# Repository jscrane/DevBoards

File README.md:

View this project on [CADLAB.io](https://cadlab.io/project/23203). 

# DevBoards
Development and breakout boards for use in Arduino projects, with Gerbers.

## t84opti
An ATtiny84 development board with FTDI interface. Works very well
with [Optiboot](https://github.com/Optiboot/optiboot),
in particular with the [ATTinyCore](https://github.com/SpenceKonde/ATTinyCore). (Top, in picture.)

## t85opti
Same as t84opti, except with ATtiny85, and no LED_BUILTIN. (Bottom, in picture.)

## nrf24l01
A breadboard adapter for the
[nrf24l01](https://howtomechatronics.com/tutorials/arduino/arduino-wireless-communication-nrf24l01-tutorial/)
short-range wireless module. (Right, in picture.)

## ncp1402
A breadboard adapter for the [ncp1402](https://www.onsemi.com/pub/Collateral/NCP1402-D.PDF)
step-up switching regulator ("boost converter"). (Left, in picture.) <i>Warning: SMD soldering required!</i>

## nrf24l01-rpi
A Raspberry Pi "hat" containing an SPI-connected nrf24l01+ radio, two status
LEDs and a shutdown button.

## d1-nrf24l01-shield
A shield for the popular Wemos D1 Mini ESP8266 board containing an SPI-connected nrf24l01+ radio.

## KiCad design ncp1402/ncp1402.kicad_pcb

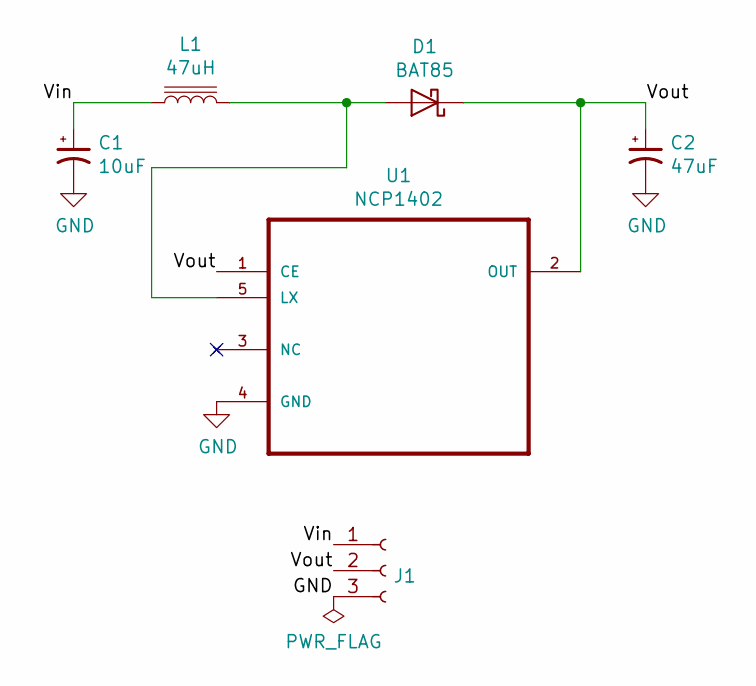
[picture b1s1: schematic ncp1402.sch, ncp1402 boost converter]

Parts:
C1: 10uF; CP_Radial_D5.0mm_P2.50mm
C2: 47uF; CP_Radial_D5.0mm_P2.50mm
D1: BAT85; D_DO-34_SOD68_P2.54mm_Vertical_KathodeUp
J1: Conn_01x03_Female; PinHeader_1x03_P2.54mm_Vertical
L1: 47uH; L_Radial_D8.7mm_P5.00mm_Fastron_07HCP
U1: NCP1402; SOT-23-5_HandSoldering

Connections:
/Vin: C1.1, J1.1, L1.1
/Vout: C2.1, D1.1 (K), J1.2, U1.1 (CE), U1.2 (OUT)
GND: C1.2, C2.2, J1.3, U1.4 (GND)
unnamed: D1.2 (A), L1.2, U1.5 (LX)

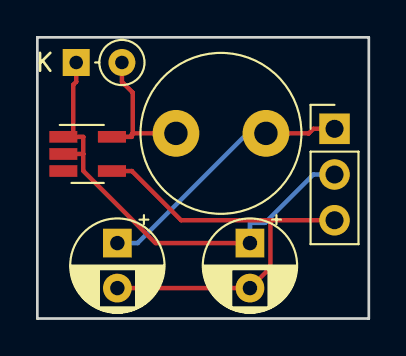
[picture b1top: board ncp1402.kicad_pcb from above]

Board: 2 copper layers, 18.4 x 15.6 mm, 6 parts (0 on the bottom side), 4 nets.

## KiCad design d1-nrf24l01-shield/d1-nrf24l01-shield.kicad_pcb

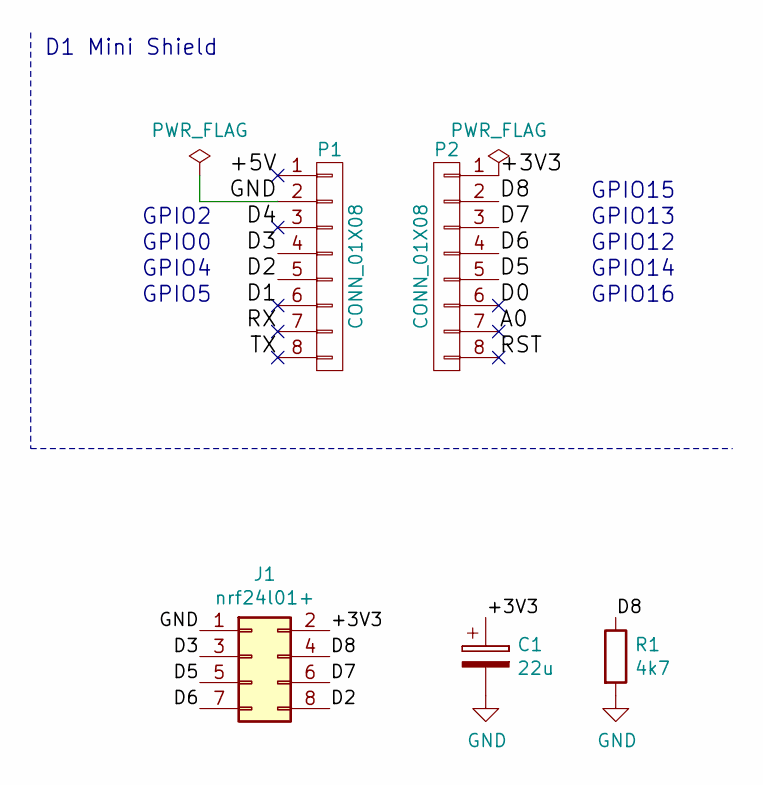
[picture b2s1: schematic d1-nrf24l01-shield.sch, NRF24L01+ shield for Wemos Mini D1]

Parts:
C1: 22u; CP_Radial_D5.0mm_P2.50mm
J1: nrf24l01+; PinHeader_2x04_P2.54mm_Vertical
P1, P2: CONN_01X08; D1_mini_Pin_Header
R1: 4k7; R_Axial_DIN0207_L6.3mm_D2.5mm_P10.16mm_Horizontal

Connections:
/+3V3: C1.1, J1.2, P2.1
/+5V: P1.1
/A0: P2.7
/D0: P2.6
/D1: P1.6
/D2: J1.8, P1.5
/D3: J1.3, P1.4
/D4: P1.3
/D5: J1.5, P2.5
/D6: J1.7, P2.4
/D7: J1.6, P2.3
/D8: J1.4, P2.2, R1.1
/RST: P2.8
/RX: P1.7
/TX: P1.8
GND: C1.2, J1.1, P1.2, R1.2

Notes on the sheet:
GPIO2
GPIO0
GPIO4
GPIO5
GPIO15
GPIO13
GPIO12
GPIO14
GPIO16
D1 Mini Shield

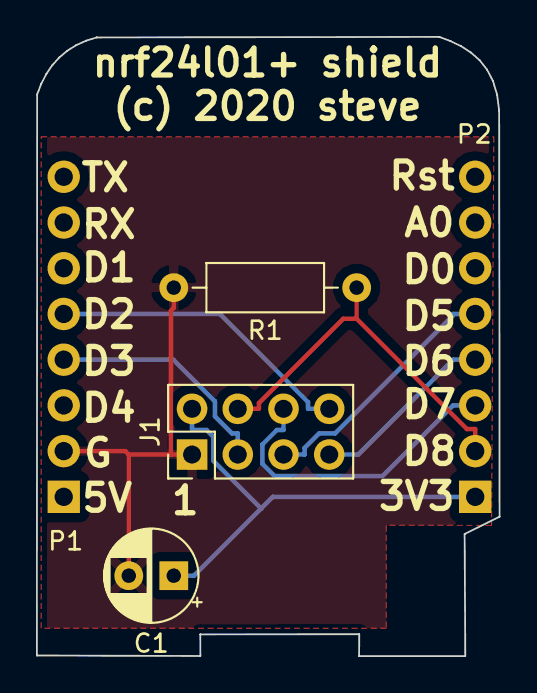
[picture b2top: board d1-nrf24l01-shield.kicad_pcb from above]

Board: 2 copper layers, 25.7 x 34.4 mm, 5 parts (0 on the bottom side), 8 nets.

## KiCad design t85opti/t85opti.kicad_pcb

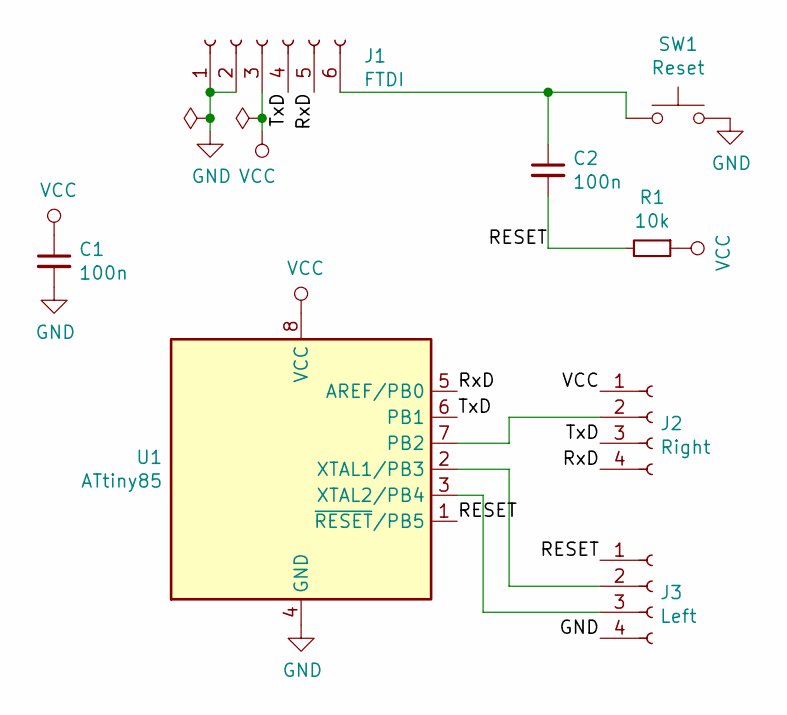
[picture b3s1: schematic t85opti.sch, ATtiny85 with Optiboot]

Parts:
C1, C2: 100n; C_Disc_D6.0mm_W2.5mm_P5.00mm
J1: FTDI; PinHeader_1x06_P2.54mm_Vertical
J2: Right; PinHeader_1x04_P2.54mm_Vertical
J3: Left; PinHeader_1x04_P2.54mm_Vertical
R1: 10k; R_Axial_DIN0207_L6.3mm_D2.5mm_P10.16mm_Horizontal
SW1: Reset; SW_PUSH_6mm_H7.3mm
U1: ATtiny85; DIP-8_W7.62mm

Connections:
/RESET: C2.2, J3.1, R1.2, U1.1 (~RESET~/PB5)
/RxD: J1.5, J2.4, U1.5 (AREF/PB0)
/TxD: J1.4, J2.3, U1.6 (PB1)
GND: C1.2, J1.1, J1.2, J3.4, SW1.2, U1.4 (GND)
unnamed: C2.1, J1.6, SW1.1
unnamed: J2.2, U1.7 (PB2)
unnamed: J3.2, U1.2 (XTAL1/PB3)
unnamed: J3.3, U1.3 (XTAL2/PB4)
VCC: C1.1, J1.3, J2.1, R1.1, U1.8 (VCC)

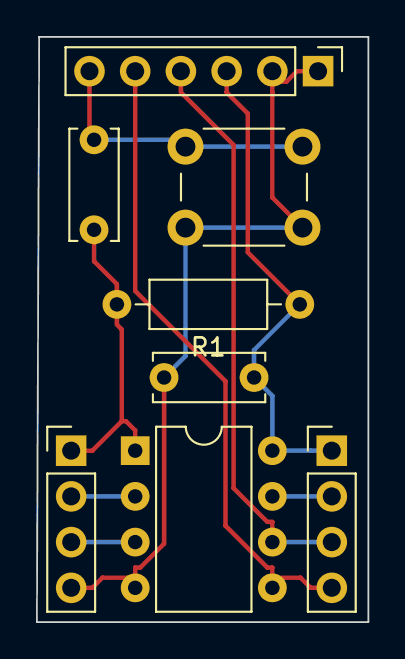
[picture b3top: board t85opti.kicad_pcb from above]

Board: 2 copper layers, 18.4 x 32.5 mm, 8 parts (0 on the bottom side), 9 nets.

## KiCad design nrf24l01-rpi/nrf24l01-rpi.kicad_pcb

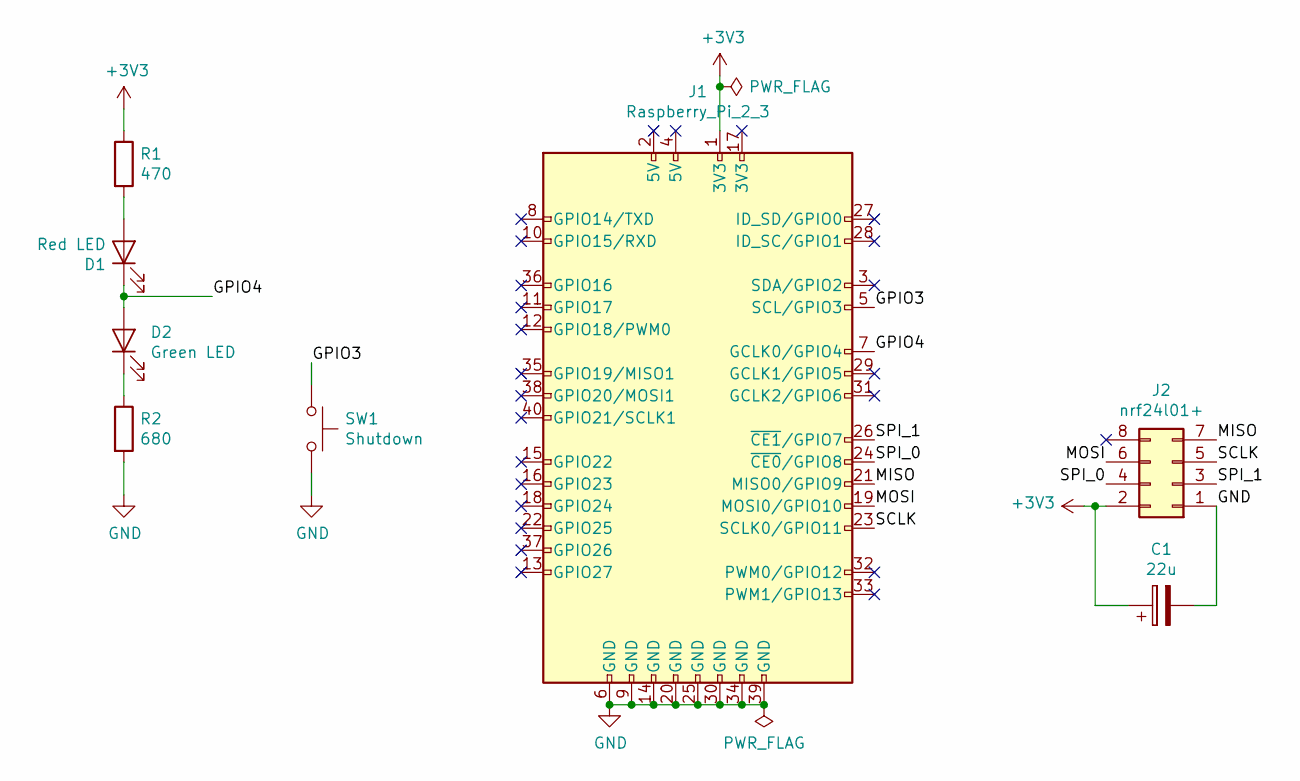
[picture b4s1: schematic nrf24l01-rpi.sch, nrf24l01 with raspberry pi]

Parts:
C1: 22u; CP_Radial_D4.0mm_P2.00mm
D1: Red LED; LED_D3.0mm
D2: Green LED; LED_D3.0mm
J1: Raspberry_Pi_2_3; PinHeader_2x20_P2.54mm_Vertical
J2: nrf24l01+; PinHeader_2x04_P2.54mm_Vertical
R1: 470; R_Axial_DIN0207_L6.3mm_D2.5mm_P7.62mm_Horizontal
R2: 680; R_Axial_DIN0207_L6.3mm_D2.5mm_P7.62mm_Horizontal
SW1: Shutdown; SW_PUSH_6mm_H7.3mm

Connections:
+3V3: C1.1, J1.1 (3V3), J2.2, R1.1
/GPIO3: J1.5 (SCL/GPIO3), SW1.1
/GPIO4: D1.1 (K), D2.2 (A), J1.7 (GCLK0/GPIO4)
/MISO: J1.21 (MISO0/GPIO9), J2.7
/MOSI: J1.19 (MOSI0/GPIO10), J2.6
/SCLK: J1.23 (SCLK0/GPIO11), J2.5
/SPI_0: J1.24 (~CE0~/GPIO8), J2.4
/SPI_1: J1.26 (~CE1~/GPIO7), J2.3
GND: C1.2, J1.6 (GND), J1.9 (GND), J1.14 (GND), J1.20 (GND), J1.25 (GND), J1.30 (GND), J1.34 (GND), J1.39 (GND), J2.1, R2.2, SW1.2
unnamed: D1.2 (A), R1.2
unnamed: D2.1 (K), R2.1

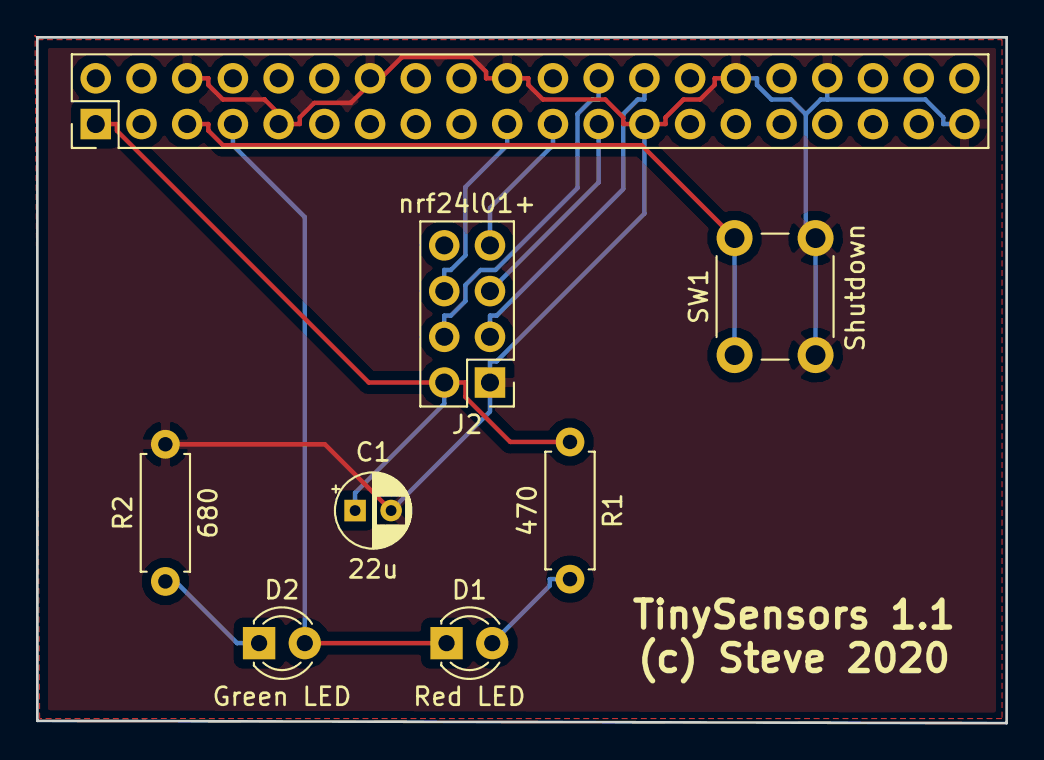
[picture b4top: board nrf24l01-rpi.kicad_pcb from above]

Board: 2 copper layers, 53.8 x 38.1 mm, 8 parts (0 on the bottom side), 11 nets.

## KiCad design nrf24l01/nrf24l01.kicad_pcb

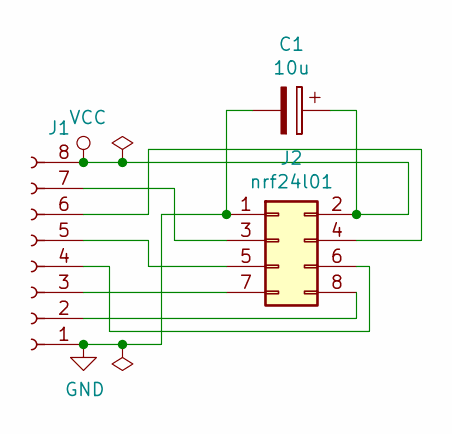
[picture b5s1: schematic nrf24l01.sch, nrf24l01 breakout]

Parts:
C1: 10u; CP_Radial_D5.0mm_P2.00mm
J1: Conn_01x08_Female; PinHeader_1x08_P2.54mm_Vertical
J2: nrf24l01; PinHeader_2x04_P2.54mm_Vertical

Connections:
GND: C1.2, J1.1, J2.1
unnamed: J1.2, J2.8
unnamed: J1.3, J2.7
unnamed: J1.4, J2.6
unnamed: J1.5, J2.5
unnamed: J1.6, J2.4
unnamed: J1.7, J2.3
VCC: C1.1, J1.8, J2.2

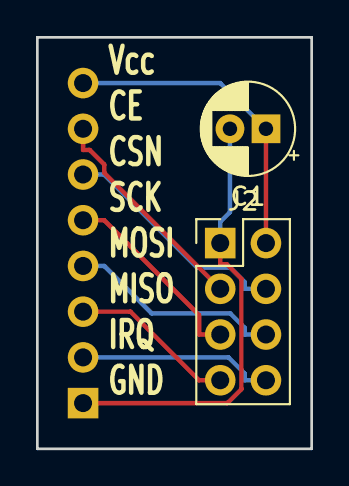
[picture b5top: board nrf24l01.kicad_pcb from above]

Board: 2 copper layers, 15.2 x 22.9 mm, 3 parts (1 on the bottom side), 8 nets.

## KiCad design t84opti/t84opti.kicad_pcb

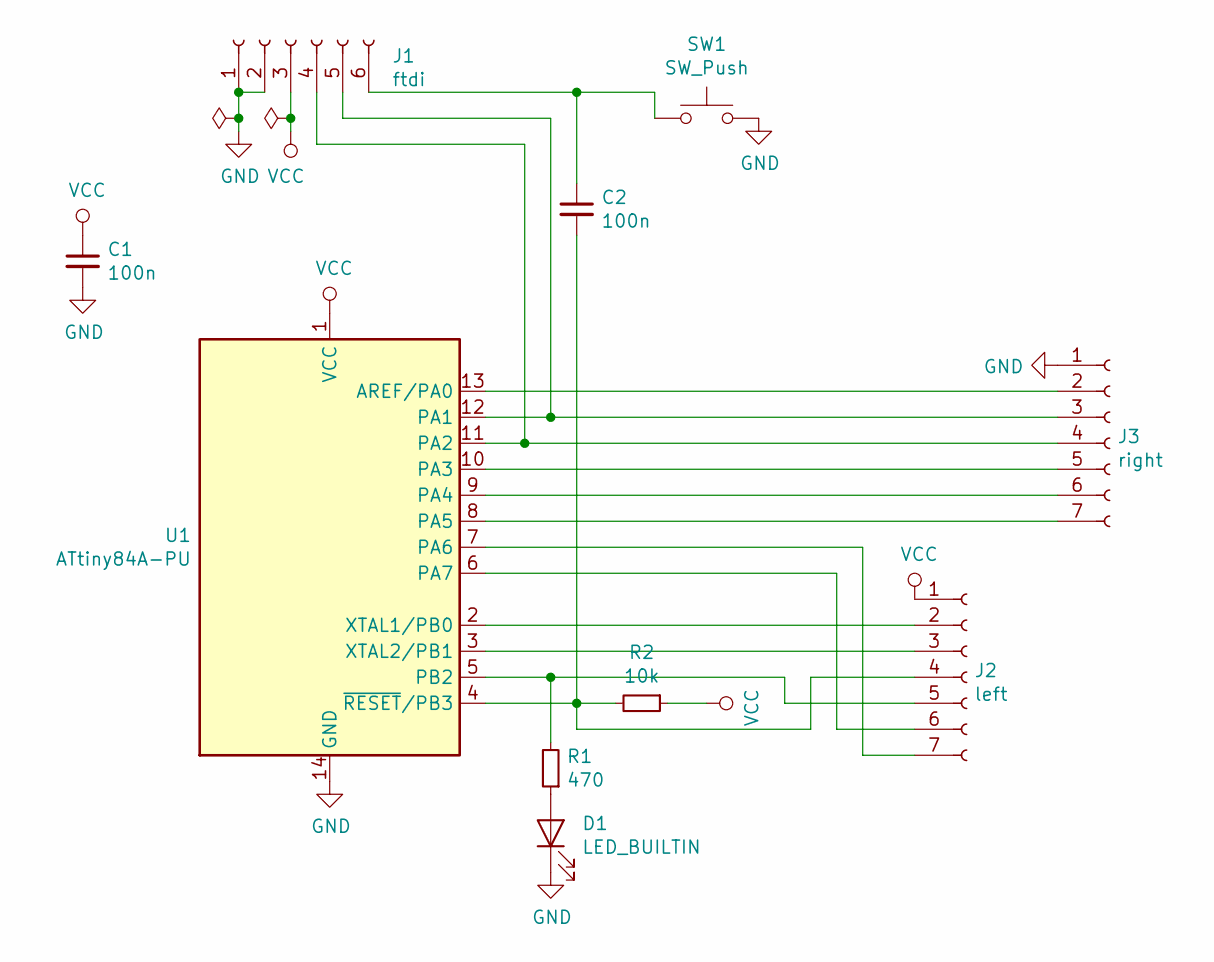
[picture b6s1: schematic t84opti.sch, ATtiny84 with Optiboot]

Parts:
C1, C2: 100n; C_Disc_D6.0mm_W2.5mm_P5.00mm
D1: LED_BUILTIN; LED_D3.0mm
J1: ftdi; PinHeader_1x06_P2.54mm_Vertical
J2: left; PinHeader_1x07_P2.54mm_Vertical
J3: right; PinHeader_1x07_P2.54mm_Vertical
R1: 470; R_Axial_DIN0207_L6.3mm_D2.5mm_P10.16mm_Horizontal
R2: 10k; R_Axial_DIN0207_L6.3mm_D2.5mm_P10.16mm_Horizontal
SW1: SW_Push; SW_PUSH_6mm_H7.3mm
U1: ATtiny84A-PU; DIP-14_W7.62mm

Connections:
GND: C1.2, D1.1 (K), J1.1, J1.2, J3.1, SW1.2, U1.14 (GND)
unnamed: C2.1, J1.6, SW1.1
unnamed: C2.2, J2.4, R2.2, U1.4 (~RESET~/PB3)
unnamed: D1.2 (A), R1.1
unnamed: J1.4, J3.4, U1.11 (PA2)
unnamed: J1.5, J3.3, U1.12 (PA1)
unnamed: J2.2, U1.2 (XTAL1/PB0)
unnamed: J2.3, U1.3 (XTAL2/PB1)
unnamed: J2.5, R1.2, U1.5 (PB2)
unnamed: J2.6, U1.6 (PA7)
unnamed: J2.7, U1.7 (PA6)
unnamed: J3.2, U1.13 (AREF/PA0)
unnamed: J3.5, U1.10 (PA3)
unnamed: J3.6, U1.9 (PA4)
unnamed: J3.7, U1.8 (PA5)
VCC: C1.1, J1.3, J2.1, R2.1, U1.1 (VCC)

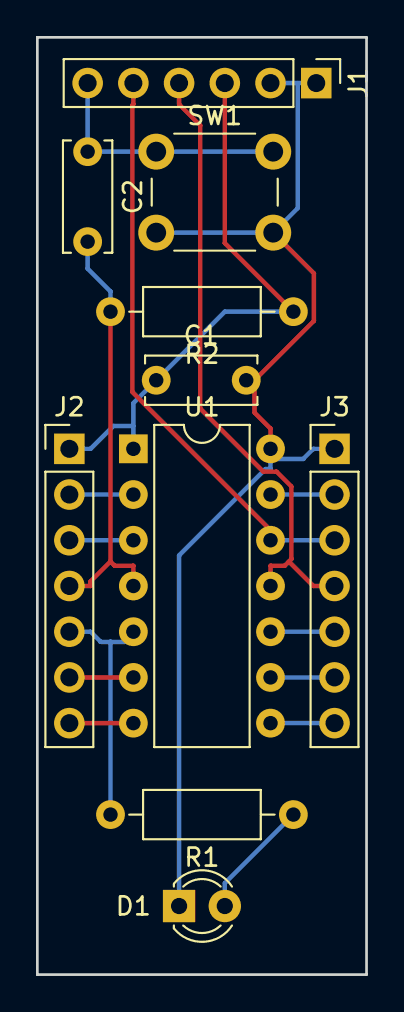
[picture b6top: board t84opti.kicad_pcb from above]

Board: 2 copper layers, 18.3 x 52.1 mm, 10 parts (0 on the bottom side), 16 nets.

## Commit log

2020-07-30 add t84opti and nrf24l01
2020-08-17 add nrf24l01-rpi
2020-08-17 add t85opti
2020-08-18 add d1-nrf24l01-shield
2020-08-18 Backlink to CADLAB.io has been added.
2020-08-26 add ncp1402
2020-09-01 add picture

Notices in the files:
d1-nrf24l01-shield/d1-nrf24l01-shield.kicad_pcb:
(c) 2020 steve
t84opti/t84opti.kicad_pcb:
(c) 2019 steve
